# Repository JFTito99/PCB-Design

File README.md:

# PCB-Design
This PCB is made for the part shown in the following hackster:
https://www.hackster.io/jft3/colorful-tunes-872243

With a potentiometer, you can control the speed of a servo which turns a color wheel. A color sensor breakout board then reads the color. The computer changes the color of an RGB LED and outputs a musical tone which can be heard on headphones connected to a plugable USB. This plugable USB is connected to a USB to micro-USB converter, which in turn can get plugged into this PCB.

Enjoy it!

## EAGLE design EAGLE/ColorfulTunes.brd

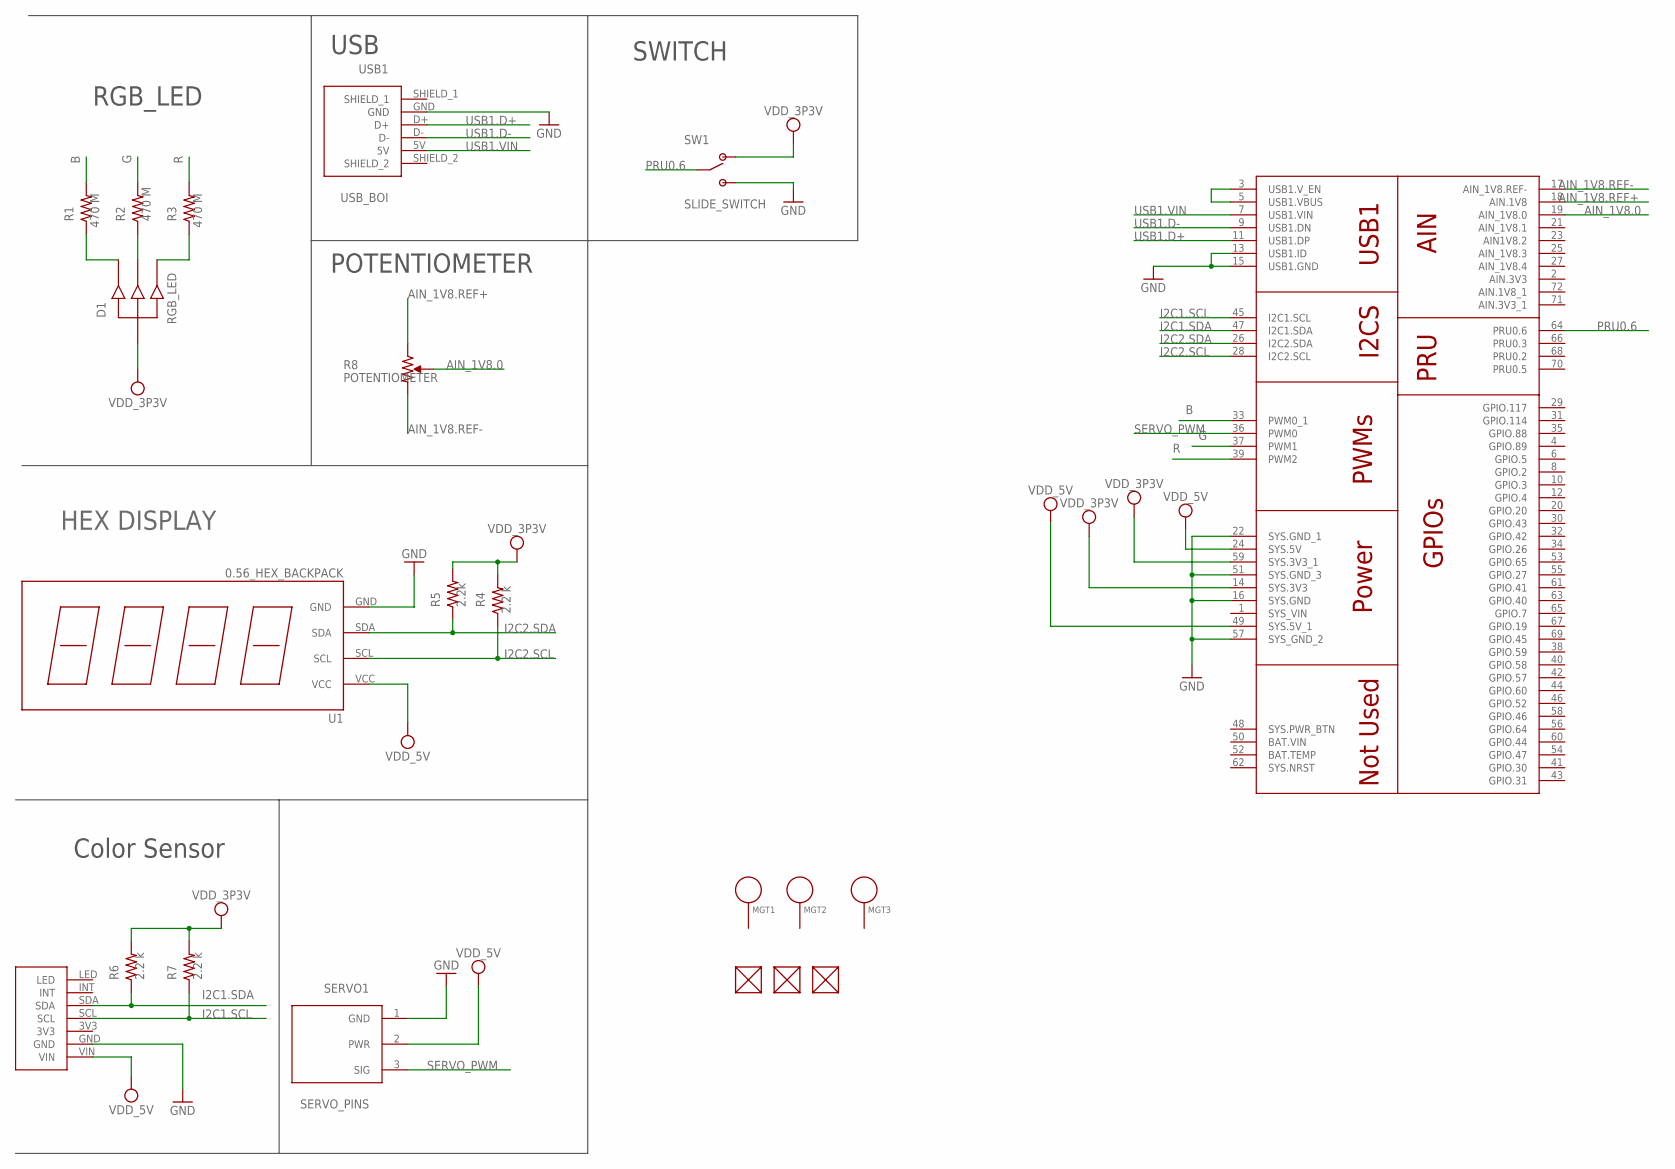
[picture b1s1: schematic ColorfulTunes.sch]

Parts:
CS1: COLOR_SENSOR_PINS; COLOR_SENSOR
D1: RGB_LED
FUD1, FUD2, FUD3: FIDUCIAL; FIDUCIAL_40MIL
MGT1, MGT2, MGT3: MOUNTING_HOLE
R1, R2, R3: 470 M; R0402
R4, R6, R7: 2.2 k; R0402
R5: 2.2k; R0402
R8: POTENTIOMETER; POT-PO90S
SERVO1: SERVO_PINS
SW1: SLIDE_SWITCH; JS202011SCQN
U1: 0.56_HEX_BACKPACK
U$1: POCKET_BEAGLE
USB1: USB_BOI

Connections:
AIN_1V8.0: R8.S, U$1.19 (AIN_1V8.0)
AIN_1V8.REF+: R8.CCW, U$1.18 (AIN.1V8)
AIN_1V8.REF-: R8.CW, U$1.17 (AIN_1V8.REF-)
B: R1.2, U$1.33 (PWM0_1)
G: R2.2, U$1.37 (PWM1)
GND: CS1.GND, SERVO1.1 (GND), SW1.3 (POS2), SW1.6 (POS2), U1.GND, U$1.13 (USB1.ID), U$1.15 (USB1.GND), U$1.16 (SYS.GND), U$1.22 (SYS.GND_1), U$1.51 (SYS.GND_3), U$1.57 (SYS_GND_2), USB1.GND
I2C1.SCL: CS1.SCL, R7.1, U$1.45 (I2C1.SCL)
I2C1.SDA: CS1.SDA, R6.1, U$1.47 (I2C1.SDA)
I2C2.SCL: R4.1, U1.SCL, U$1.28 (I2C2.SCL)
I2C2.SDA: R5.1, U1.SDA, U$1.26 (I2C2.SDA)
unnamed: D1.2 (PWM1), R1.1
unnamed: D1.3 (PWM2), R2.1
unnamed: D1.4 (PWM3), R3.1
unnamed: U$1.3 (USB1.V_EN), U$1.5 (USB1.VBUS)
PRU0.6: SW1.2 (COMM), SW1.5 (COMM), U$1.64 (PRU0.6)
R: R3.2, U$1.39 (PWM2)
SERVO_PWM: SERVO1.3 (SIG), U$1.36 (PWM0)
SYS_VIN: U$1.1 (SYS_VIN)
USB1.D+: U$1.11 (USB1.DP), USB1.D+
USB1.D-: U$1.9 (USB1.DN), USB1.D-
USB1.VIN: U$1.7 (USB1.VIN), USB1.5V
VDD_3P3V: D1.1 (PWR), R4.2, R5.2, R6.2, R7.2, SW1.1 (POS1), SW1.4 (POS1), U$1.14 (SYS.3V3), U$1.59 (SYS.3V3_1)
VDD_5V: CS1.VIN, SERVO1.2 (PWR), U1.VCC, U$1.24 (SYS.5V), U$1.49 (SYS.5V_1)

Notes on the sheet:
RGB_LED
HEX DISPLAY
Color Sensor
USB
POTENTIOMETER
SWITCH

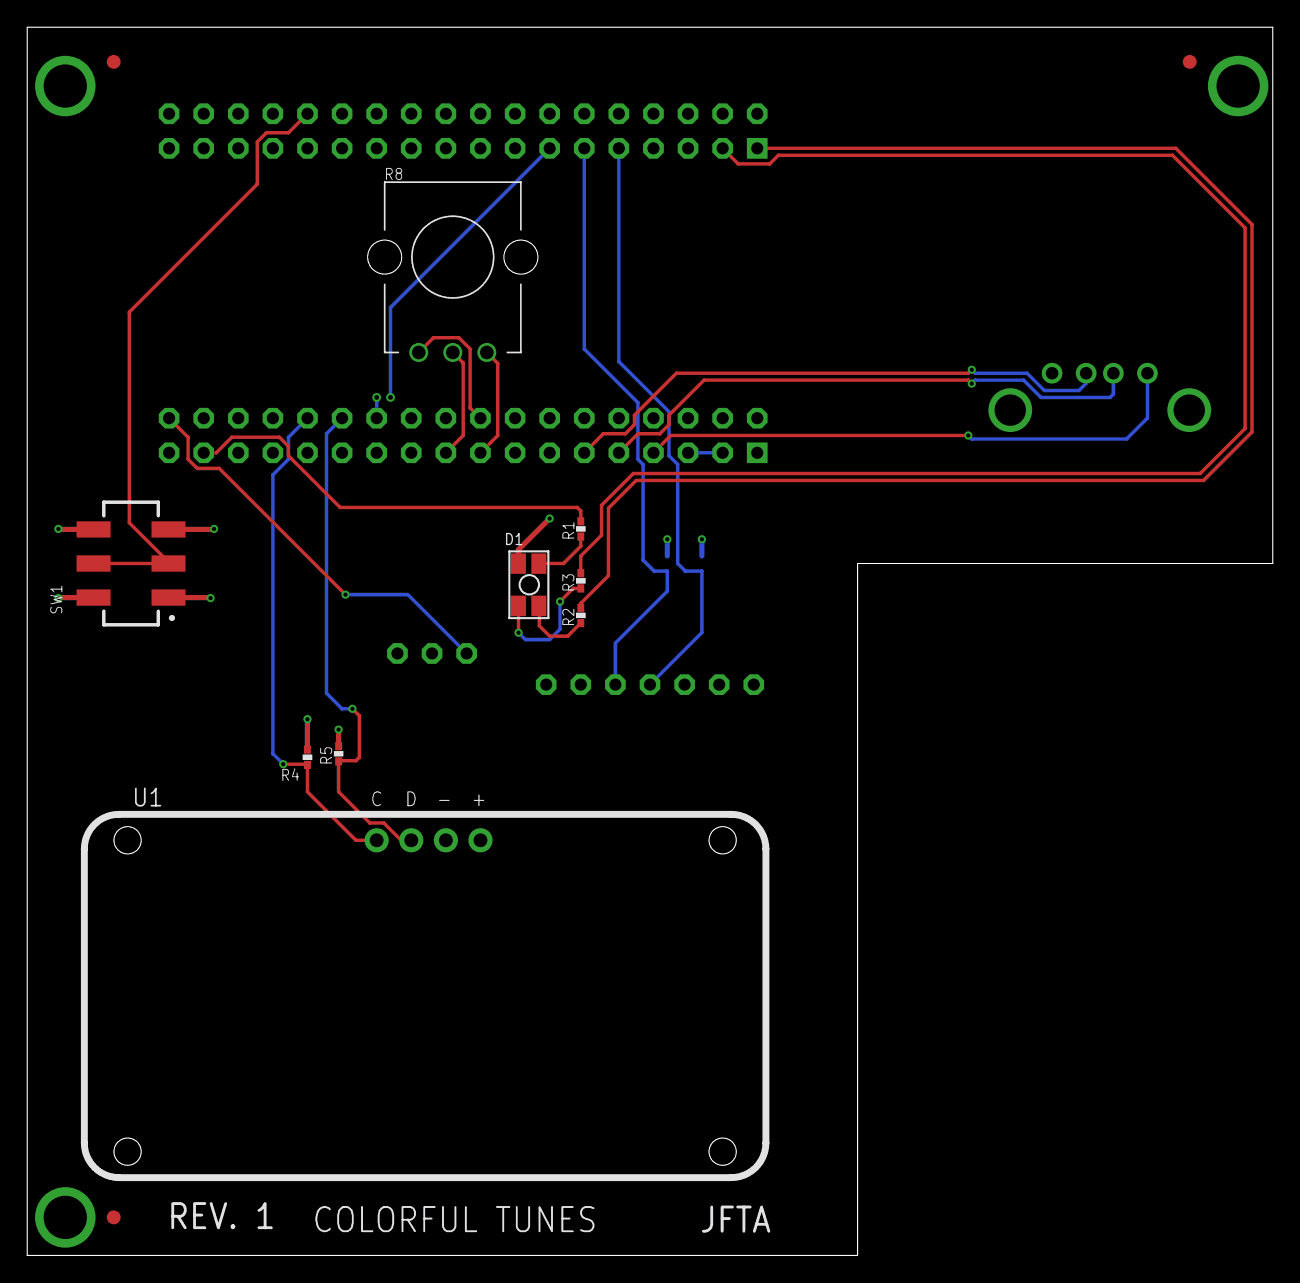
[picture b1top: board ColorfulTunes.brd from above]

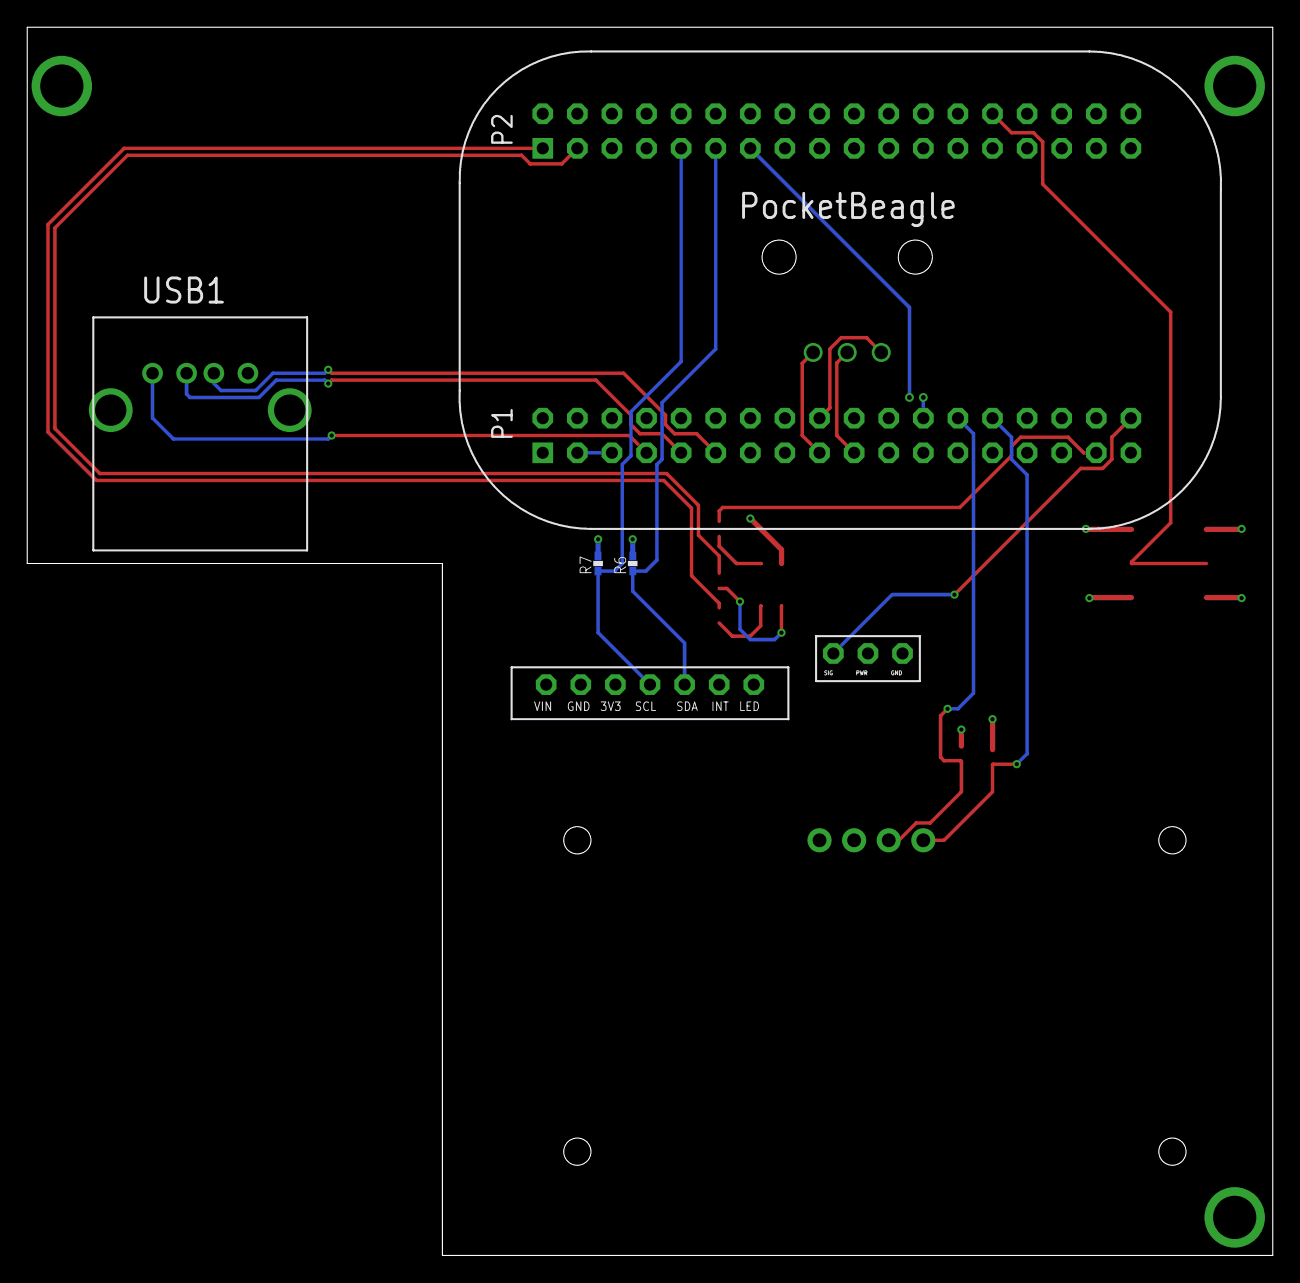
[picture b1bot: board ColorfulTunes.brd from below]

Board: 4 copper layers, 91.4 x 90.2 mm, 21 parts (6 on the bottom side), 22 nets.

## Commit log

2019-12-16 First thing saved!
2019-12-17 Progress!
2019-12-17 Please check this schematic :)
2019-12-17 Found some mistakes, please check this one. Thank you!
2019-12-18 Removing Unecessary Stuff
2019-12-18 Am I really done? Is there really justice in this cold dark world?
2019-12-18 Almost there!
2019-12-18 with the mounting holes
2019-12-18 Top and Bottom layers
2019-12-18 More clean and nice version
2019-12-18 BOM additions
2019-12-18 PDF of project
2019-12-18 Renaming file
2019-12-18 no message
2019-12-18 CAM files
